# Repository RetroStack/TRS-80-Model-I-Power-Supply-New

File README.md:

# TRS-80 Model 1 - Power Supply

This project is a reimplementation of the TRS-80 Model 1 Power Supply that replicates the DC and AC voltages needed to run the original system. This revision is based on [previous work](https://github.com/maboytim/TRS-80_Model1_Power_Supply) by Matt Boytim, with slight modifications to that design. The entire project is available under the MIT license, while the reference project has been released into the Public Domain.

This version supports both 120V and 230V.

**NOTE**: A [previous power supply](https://github.com/RetroStack/TRS-80-Model-I-Power-Supply) was released by RetroStack. This new version replaces that power supply as it is cheaper to produce, lighter, and smaller.

**WARNING**: This project involves high voltages that can cause severe injury, death, or property damage. Only proceed if you have the necessary experience and knowledge in handling high-voltage electronics.

- **Safety First**: Always unplug the device and ensure it is fully discharged before beginning any work. Capacitors can store a significant amount of energy. Use insulated tools and wear appropriate safety gear, such as rubber gloves and safety glasses.
- **Risk of Fire and Shock**: Incorrect wiring or assembly can lead to electric shock, fire, or malfunction. Double-check all connections, and if you're unsure, consult a qualified electrician or engineer. As this is a hobby device, never leave it connected without supervision.
- **Use at Your Own Risk**: The creator of this project is not liable for any damage, injury, or harm caused by the misuse of these instructions. Proceed with extreme caution and at your own risk.

## Project Details

### Latest Files

In the "Latest" folder, you'll find the most up-to-date design files, including:

- Gerber files suitable for popular online PCB manufacturers like [PCBWay](/Latest/Gerber_PCBWay.zip) and [JLCPCB](/Latest/Gerber_JLCPCB.zip). Most manufacturers should be fine with either.
- A Bill of Materials (BOM) in both [CSV](/Latest/BOM.csv) and [PDF](/Latest/BOM.pdf) formats. (Also, see the list below.)
- The [full schematics](/Latest/Schematics.pdf).
- 3D Objects (only need base and lid for full assembly):
  - [Base](/Latest/3DPrint_Base.stl)
  - Lid
    - For resin printing: [Lid](/Latest/3DPrint_Lid.stl) and [Plain Lid](/Latest/3DPrint_Lid_Plain.stl)
    - For FPM printing: [Lid](/Latest/3DPrint_Lid_FPM.stl) and [Plain Lid](/Latest/3DPrint_Lid_FPM_Plain.stl)
  - Optional [Label](/Latest/3DPrint_Label.stl): Saves on printing suport with FPM or enables printing a badge for plain models

### Bill of Materials (BOM)

| Reference | Qty | Value      | Footprint                                                   | Source                                                                                                                 |
| --------- | --- | ---------- | ----------------------------------------------------------- | ---------------------------------------------------------------------------------------------------------------------- |
| C1,C2     | 2   | 2200u      | Capacitor_THT:CP_Radial_D12.5mm_P5.00mm                     | [Mouser](https://www.mouser.com/ProductDetail/647-UVR1C222MHD1TO)                                                      |
| D1        | 1   | B40C800G   | Diode_THT:Diode_Bridge_Round_D9.8mm                         | [Mouser](https://www.mouser.com/ProductDetail/625-B40C800G-E4)                                                         |
| T1        | 1   |            | ST-6-16 (110V) or DST-6-16 (220V)                           | Mouser [ST](https://www.mouser.com/ProductDetail/530-ST-6-16) [DST](https://www.mouser.com/ProductDetail/530-DST-6-16) |
| -         | 1   | Power Unit | With Fuse, Switch and C8 connector                          | [AliExpress](https://www.aliexpress.us/item/3256805889410008.html)                                                     |
| -         | 1   | Case       | Top                                                         | [JLCPCB](https://jlc3dp.com/3d-printing-quote)                                                                         |
| -         | 1   | Case       | Bottom                                                      | [JLCPCB](https://jlc3dp.com/3d-printing-quote)                                                                         |
| -         | 2   | M3         | Screw; 40mm length or longer (for Transformer); Sunken Head |                                                                                                                        |
| -         | 2   | M3         | Nut (for Transformer)                                       |                                                                                                                        |
| -         | 4   | M3         | Screw; 10mm length (for Case); Sunken Head                  |                                                                                                                        |
| -         | 2   | M3         | Screw; 6mm length (for power unit); Black                   |                                                                                                                        |
| -         | 1   | 6N-4       | Strain Relief                                               | [AliExpress](https://www.aliexpress.us/item/3256804453313992.html)                                                     |
| -         | 1   | Cable      | 4 or 5-wires (5 preferred); ~50cm length                    |                                                                                                                        |
| -         | 1   | DIN-5      | Connector                                                   |                                                                                                                        |
| -         | 1   | Zip-Tie    | To improve strain relief                                    |                                                                                                                        |
| -         | 1   | Fuse       | 1.5A 250V; 6x30mm Glass Fuse; Fast Blow                     |                                                                                                                        |
| -         | -   | Wire       | AWG 20 (or lower) for power connection                      |                                                                                                                        |

### Assembly

**Prepare Case**

1.  3D print the case (lid and base) or order it from a manufacturer.
2.  a. If 3D printed with PLA or similar material, use a soldering iron to set the knurled nuts. You can purchase a set of tools to simplify this, but a soldering iron is sufficient.

    b. If 3D printed with resin, set the knurled nuts with super glue or similar. Be careful not to cover the threads with glue, as this will cause problems when screwing things in later on. Wait until the glue is fully set before moving on.

4. Paint the lettering on the top. I achieved good results using a foam brush or Q-tip. Optionally, apply a clear coat to protect the paint from wearing off.
5. (Optional) If the label object is printed with a plain lid, simply glue the label on top of the lid.

**Electronics**

1. Solder in the transformer. Match the numbers written on the terminals to the numbers on the PCB. If you're using the ST-6-16, terminals 2 and 3 will be missing, which is fine. These are only used for the DST-6-16.
2. Solder in the two capacitors. They are polarized, so ensure the negatively marked sides match the PCB silkscreen.
3. Solder in the rectifier, aligning the direction with the PCB silkscreen.
4. Solder a 5-wire cable to the secondary side of the transformer, between the capacitors. Ideally, match a red wire to the center (~20V DC), a green/yellow wire to the outer AC connections, and a black/white wire to the two positions adjacent to the center (for ground). Matching colors or jotting down the wire colors will help you later when soldering the DIN-5 connector. You can also use a 4-wire cable, but in that case, choose only one ground pad instead of both.
5. _(Optional)_ Add a cable tie around the cable for extra strain relief.

6. Crimp two short wires to create jumpers: one between the terminal and the switch, and another from the fuse to the switch. Connect the first wire (from the connector, not the fuse) to the switch's common terminal, which is usually marked with a different color. One side of the switch will be for the light (you can typically see the lightbulb leads). Use the opposite side so the light turns on only when the switch is activated. If it's incorrect, you can swap them later. I used AWG 20 wire for this.
7. Crimp two more wires on one side, each connecting to the other side of the switch and carrying the 110V/220V AC. I used AWG 20 wire. Depending on your power unit (see below), different connections may be required.

**NOTE:** There are different configurations for the power unit. Here’s another setup I've used in the past:

8. Solder the last two wires into place on one side of the PCB (the primary side). Leave them disconnected from the power unit for now.
9. Screw in the transformer and PCB using long M4 screws and nuts.
10. Screw in the power unit. First, pull out the two crimped cables and connect them to the remaining terminals on the power unit before screwing it in.
11. Assemble the case using the smaller M3 screws.
12. Add the plastic grommet for strain relief.

13. Solder the DIN-5 connector according to this diagram:

14. Insert the fuse into the fuse holder.

### Implementation

The project has been implemented using KiCAD 8. The KiCAD project files are included in this repository.

### 3D Objects

The project includes various types of 3D objects for self-printing. It offers a set of bases and lids for resin prints, where the screw inserts must be glued in place, while the FPM version features slightly smaller holes designed for heat setting. Additionally, plain lids with separate label objects are provided, allowing the label and lid to be printed separately. This reduces the need for supports and enhances overall print quality.

### RetroStack Libraries

To work with this KiCAD project, you'll need the RetroStack libraries for KiCAD. Please [follow this link](https://www.github.com/RetroStack/KiCAD-Libraries) to access and install these libraries.

## Main TRS-80 Model 1 Repository

For additional resources related to the TRS-80 Model 1, be sure to check out the central page for the TRS-80 Model 1 on RetroStack. You can find it [here](https://www.github.com/RetroStack/TRS-80-Model-I).

## Support this Project

RetroStack is passionate about exploring and preserving the legacy of older computer systems. My work involves creating detailed documentation and videos to share the knowledge. I am also dedicated to reviving these classic systems by reimplementing them and offering replacement parts at no cost. If you're keen on supporting this unique project, I invite you to visit my [Patreon page](https://www.patreon.com/RetroStack). Your support would be immensely valuable and greatly appreciated!

## License

This project is licensed under the MIT License - see the [LICENSE](LICENSE) file for details.

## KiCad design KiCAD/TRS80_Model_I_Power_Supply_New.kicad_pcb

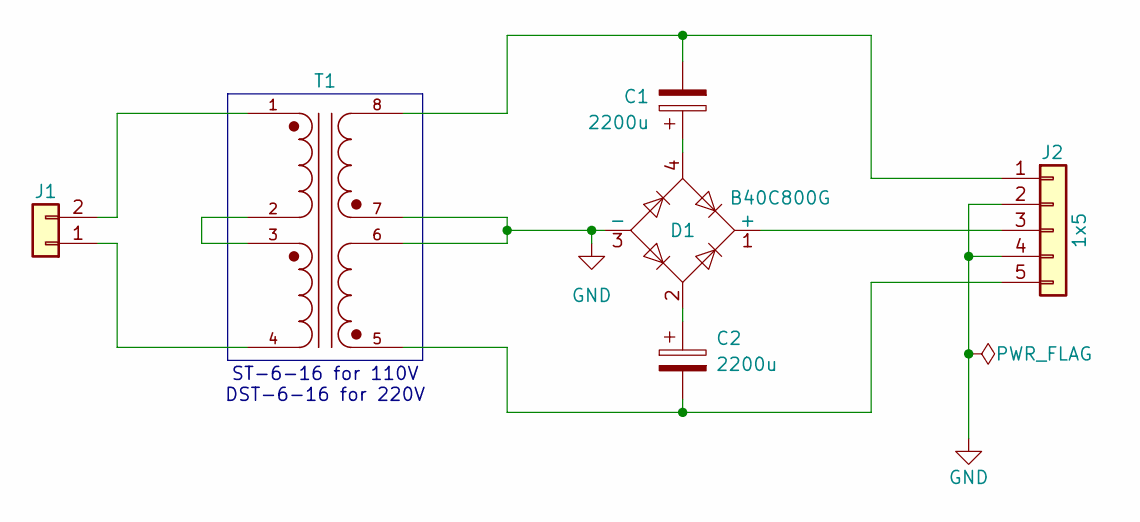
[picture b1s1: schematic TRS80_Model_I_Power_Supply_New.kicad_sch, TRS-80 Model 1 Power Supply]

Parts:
C1, C2: 2200u; CP_Radial_D12.5mm_P5.00mm
D1: B40C800G; Diode_Bridge_Round_D9.8mm
J1: Conn_01x02; Molex_KK-396_A-41791-0002_1x02_P3.96mm_Vertical
J2: 1x5; Molex_KK-254_AE-6410-05A_1x05_P2.54mm_Vertical
T1: DST-6-16; XFMR_DST-6-16; PARTREV 2019

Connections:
GND: D1.3 (-), J2.2, J2.4, T1.6, T1.7
unnamed: C1.1, D1.4
unnamed: C2.1, D1.2
unnamed: D1.1 (+), J2.3
unnamed: J1.1, T1.4
unnamed: J1.2, T1.1
unnamed: C1.2, J2.1, T1.8
unnamed: C2.2, J2.5, T1.5
unnamed: T1.2, T1.3

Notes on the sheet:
ST-6-16 for 110V DST-6-16 for 220V

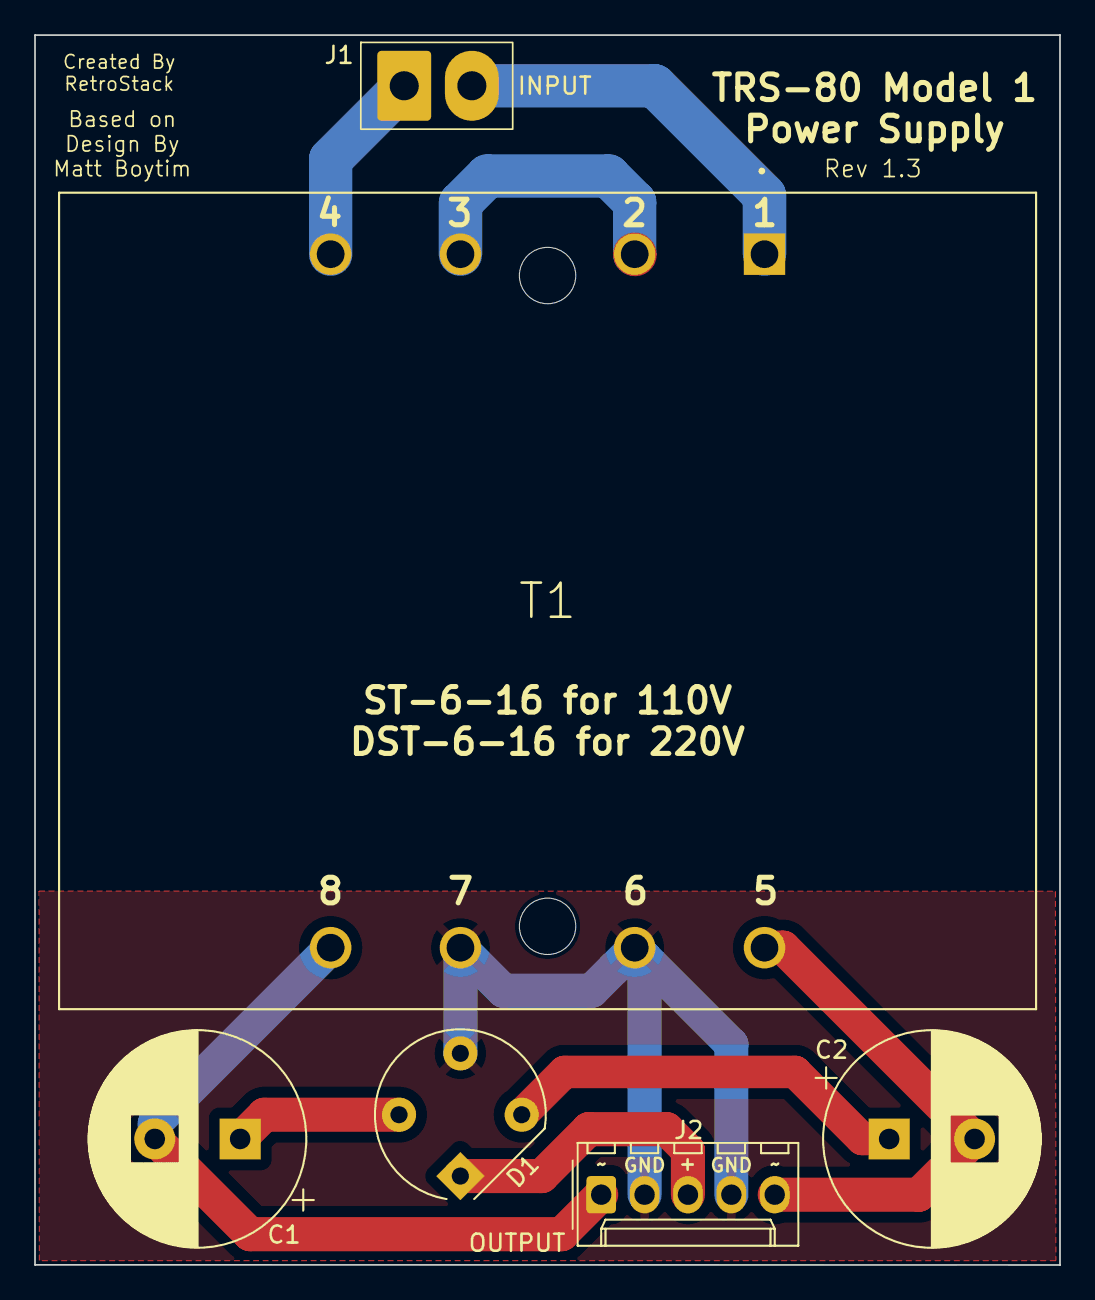
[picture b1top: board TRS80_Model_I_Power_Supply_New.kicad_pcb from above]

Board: 2 copper layers, 60.0 x 72.0 mm, 6 parts (0 on the bottom side), 9 nets.

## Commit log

2024-10-03 Update to latest version
2024-10-05 Improved documentation
2024-10-30 Add plain lid
2024-11-07 Update README.md
    Adding sources
2024-11-07 Regenerate Gerber Files
2024-12-19 3D Model modifications
